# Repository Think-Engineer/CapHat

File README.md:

# CAPHAT - Capactive Touch Keypad for the Raspberry Pi

All the software, hardware and examples for building apps with the CapHat capacitive touch keypads. 

Check out our successful [Kickstarter](https://www.kickstarter.com/projects/364371217/caphat-a-raspberry-pi-capacitive-keypad-hat-access/description) for more details on what it does.

## Installation
We've attempted to capture everything you need to do in order to get your CapHat up and running with our example demo. You can follow the installation guide [here](documentation/installation.md)

## Contributing

1. Fork it!
2. Create your feature branch: `git checkout -b my-new-feature`
3. Commit your changes: `git commit -am 'Add some feature'`
4. Push to the branch: `git push origin my-new-feature`
5. Submit a pull request :D

We'd love to incorporate your demos into this project. The better documented your PR is the more likely we'll accept it!

## License

We've licensed the CapHat under MIT, this includes all hardware & software. Feel free to read our [License.md](License.md)

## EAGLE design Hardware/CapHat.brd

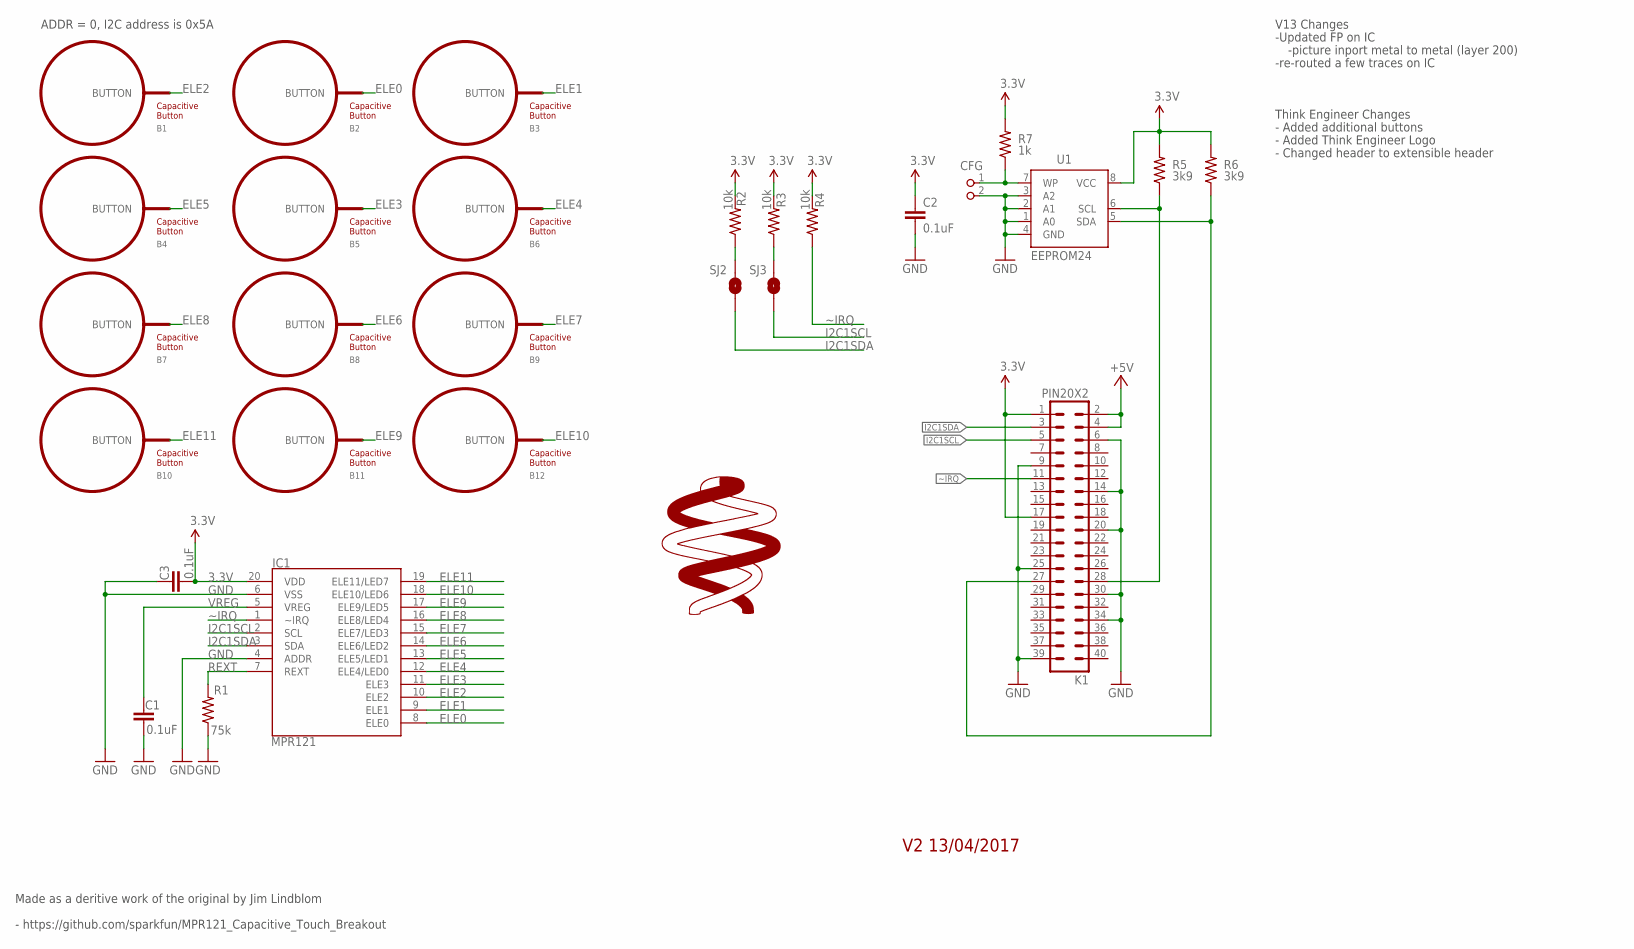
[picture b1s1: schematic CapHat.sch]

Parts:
B1, B2, B3, B4, B5, B6, B7, B8, B9, B10, B11, B12: BUTTON_PASSIVE10MM; BUTTON_PASSIVE_10MM
C1, C2, C3: 0.1uF; 0603-CAP
CFG: PIN2_100; PIN_W_2
IC1: MPR121; QFN-20-0.4MM-V2
K1: PIN20X2; PIN_20X2
R1: 75k; 0603-RES
R2, R3, R4: 10k; 0603-RES
R5, R6: 3k9; 0603-RES; TOLERANCE 5%
R7: 1k; 0603-RES; TOLERANCE 5%
SJ2, SJ3: SOLDERJUMPERNO; SJ_2S-NO
U1: EEPROM24; SOIC8
U$1: THINK_LOGO

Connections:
3.3V: C2.1, C3.2, IC1.20 (VDD), K1.1, K1.17, R2.2, R3.2, R4.2, R5.2, R6.2, R7.2, U1.8 (VCC)
+5V: K1.2, K1.4
ELE0: B2.BUTTON, IC1.8 (ELE0)
ELE1: B3.BUTTON, IC1.9 (ELE1)
ELE2: B1.BUTTON, IC1.10 (ELE2)
ELE3: B5.BUTTON, IC1.11 (ELE3)
ELE4: B6.BUTTON, IC1.12 (ELE4/LED0)
ELE5: B4.BUTTON, IC1.13 (ELE5/LED1)
ELE6: B8.BUTTON, IC1.14 (ELE6/LED2)
ELE7: B9.BUTTON, IC1.15 (ELE7/LED3)
ELE8: B7.BUTTON, IC1.16 (ELE8/LED4)
ELE9: B11.BUTTON, IC1.17 (ELE9/LED5)
ELE10: B12.BUTTON, IC1.18 (ELE10/LED6)
ELE11: B10.BUTTON, IC1.19 (ELE11/LED7)
GND: C1.2, C2.2, C3.1, CFG.2, IC1.4 (ADDR), IC1.6 (VSS), K1.6, K1.9, K1.14, K1.20, K1.25, K1.30, K1.34, K1.39, R1.1, U1.1 (A0), U1.2 (A1), U1.3 (A2), U1.4 (GND)
I2C1SCL: IC1.2 (SCL), K1.5, SJ3.1
I2C1SDA: IC1.3 (SDA), K1.3, SJ2.1
unnamed: K1.28, R5.1, U1.6 (SCL)
unnamed: K1.27, R6.1, U1.5 (SDA)
unnamed: CFG.1, R7.1, U1.7 (WP)
REXT: IC1.7 (REXT), R1.2
SCL_PU: R3.1, SJ3.2
SDA_PU: R2.1, SJ2.2
VREG: C1.1, IC1.5 (VREG)
~IRQ: IC1.1 (~IRQ), K1.11, R4.1

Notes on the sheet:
ADDR = 0, I2C address is 0x5A
Made as a deritive work of the original by Jim Lindblom
V13 Changes
-Updated FP on IC
-picture inport metal to metal (layer 200)
-re-routed a few traces on IC
- https://github.com/sparkfun/MPR121_Capacitive_Touch_Breakout
Think Engineer Changes
- Added additional buttons
- Added Think Engineer Logo
- Changed header to extensible header
V2 13/04/2017

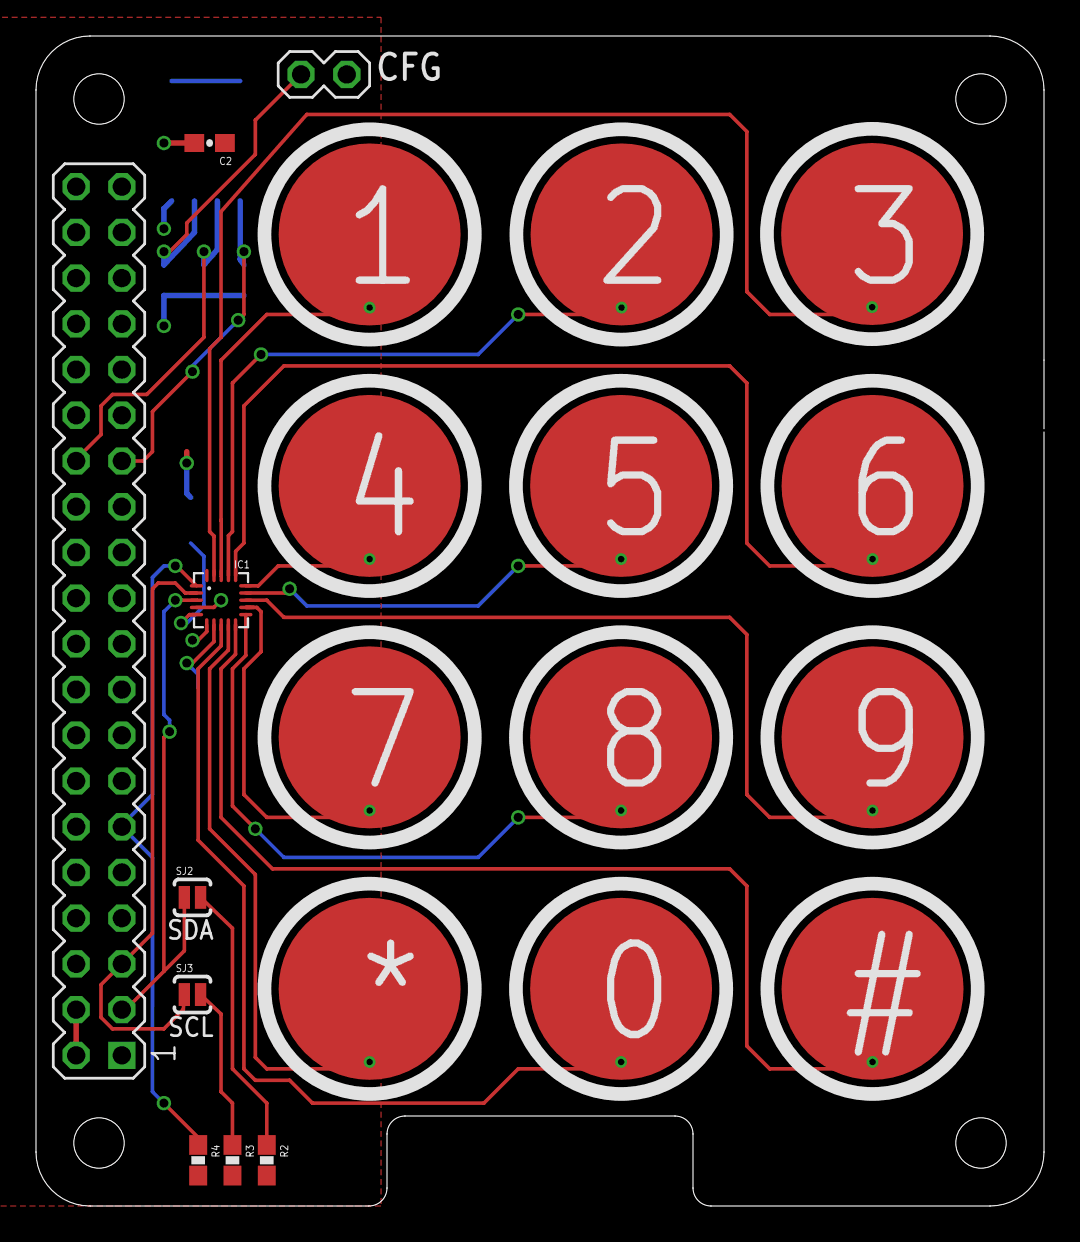
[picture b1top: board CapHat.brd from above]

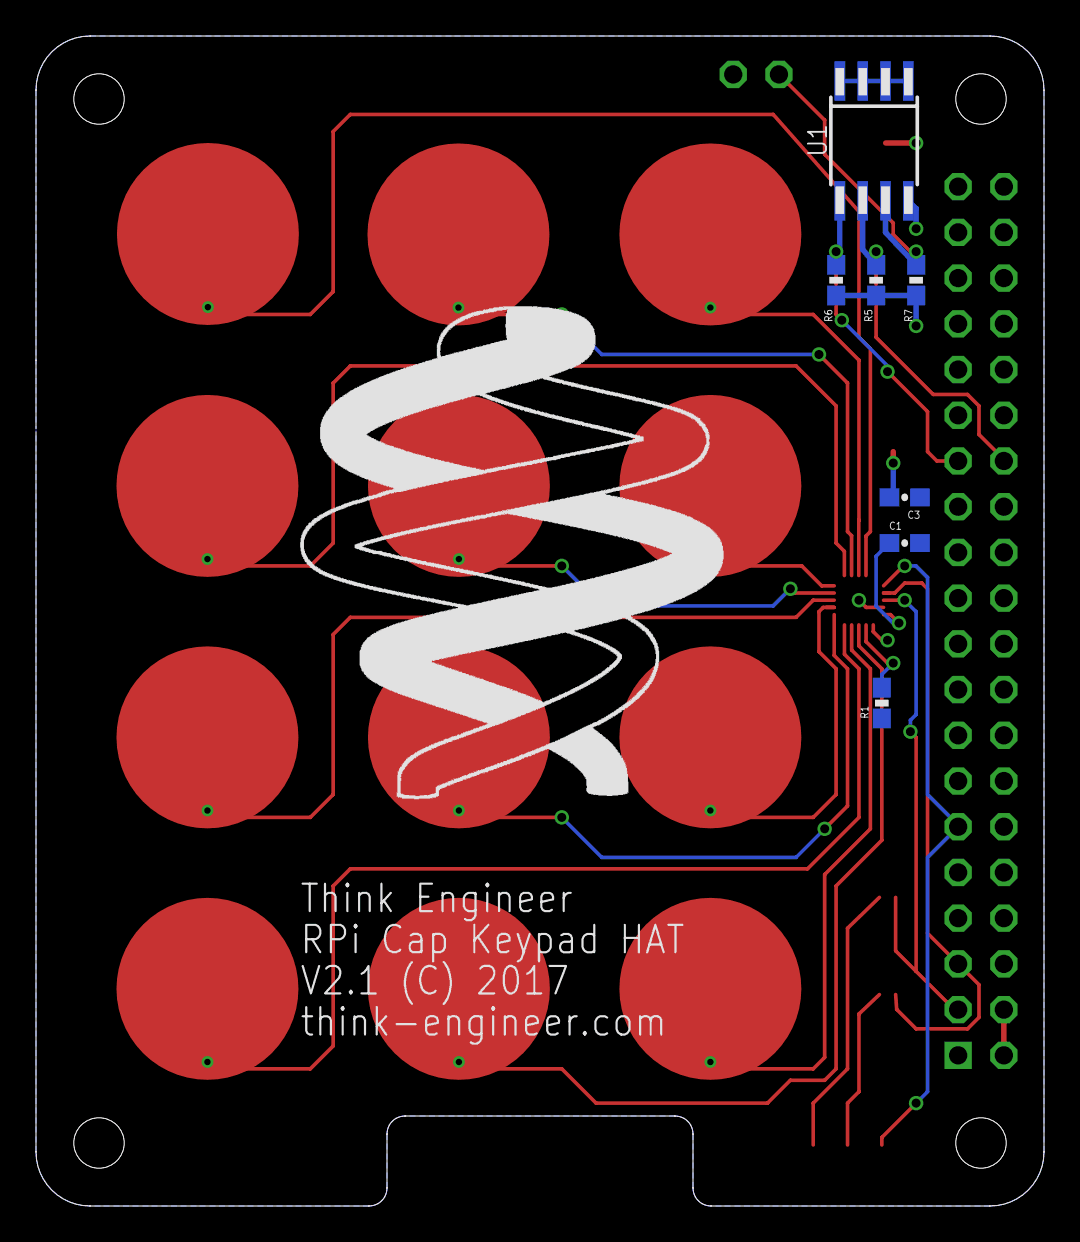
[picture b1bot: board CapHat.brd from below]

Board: 2 copper layers, 56.0 x 65.0 mm, 29 parts (8 on the bottom side), 25 nets.

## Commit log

2017-04-13 V2.0 Schematic & PCB Eagle Files
2017-05-24 Adafruit Library, Examples, Readme & Installation Guide placeholder
2017-05-24 Added Installation guide
2017-05-24 Compressed image to make it much smaller.
2017-05-24 Fixed image path

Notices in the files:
Hardware/CapHat.brd:
V2.1 (C) 2017
parts and their libraries:
PatternAgents-TouchWidgets: License : http://creativecommons.org/licenses/by-sa/4.0/ (Creative Commons 4.0)
PatternAgents-TouchWidgets: License : http://creativecommons.org/licenses/by-sa/3.1/ (Creative Commons 3.1)
